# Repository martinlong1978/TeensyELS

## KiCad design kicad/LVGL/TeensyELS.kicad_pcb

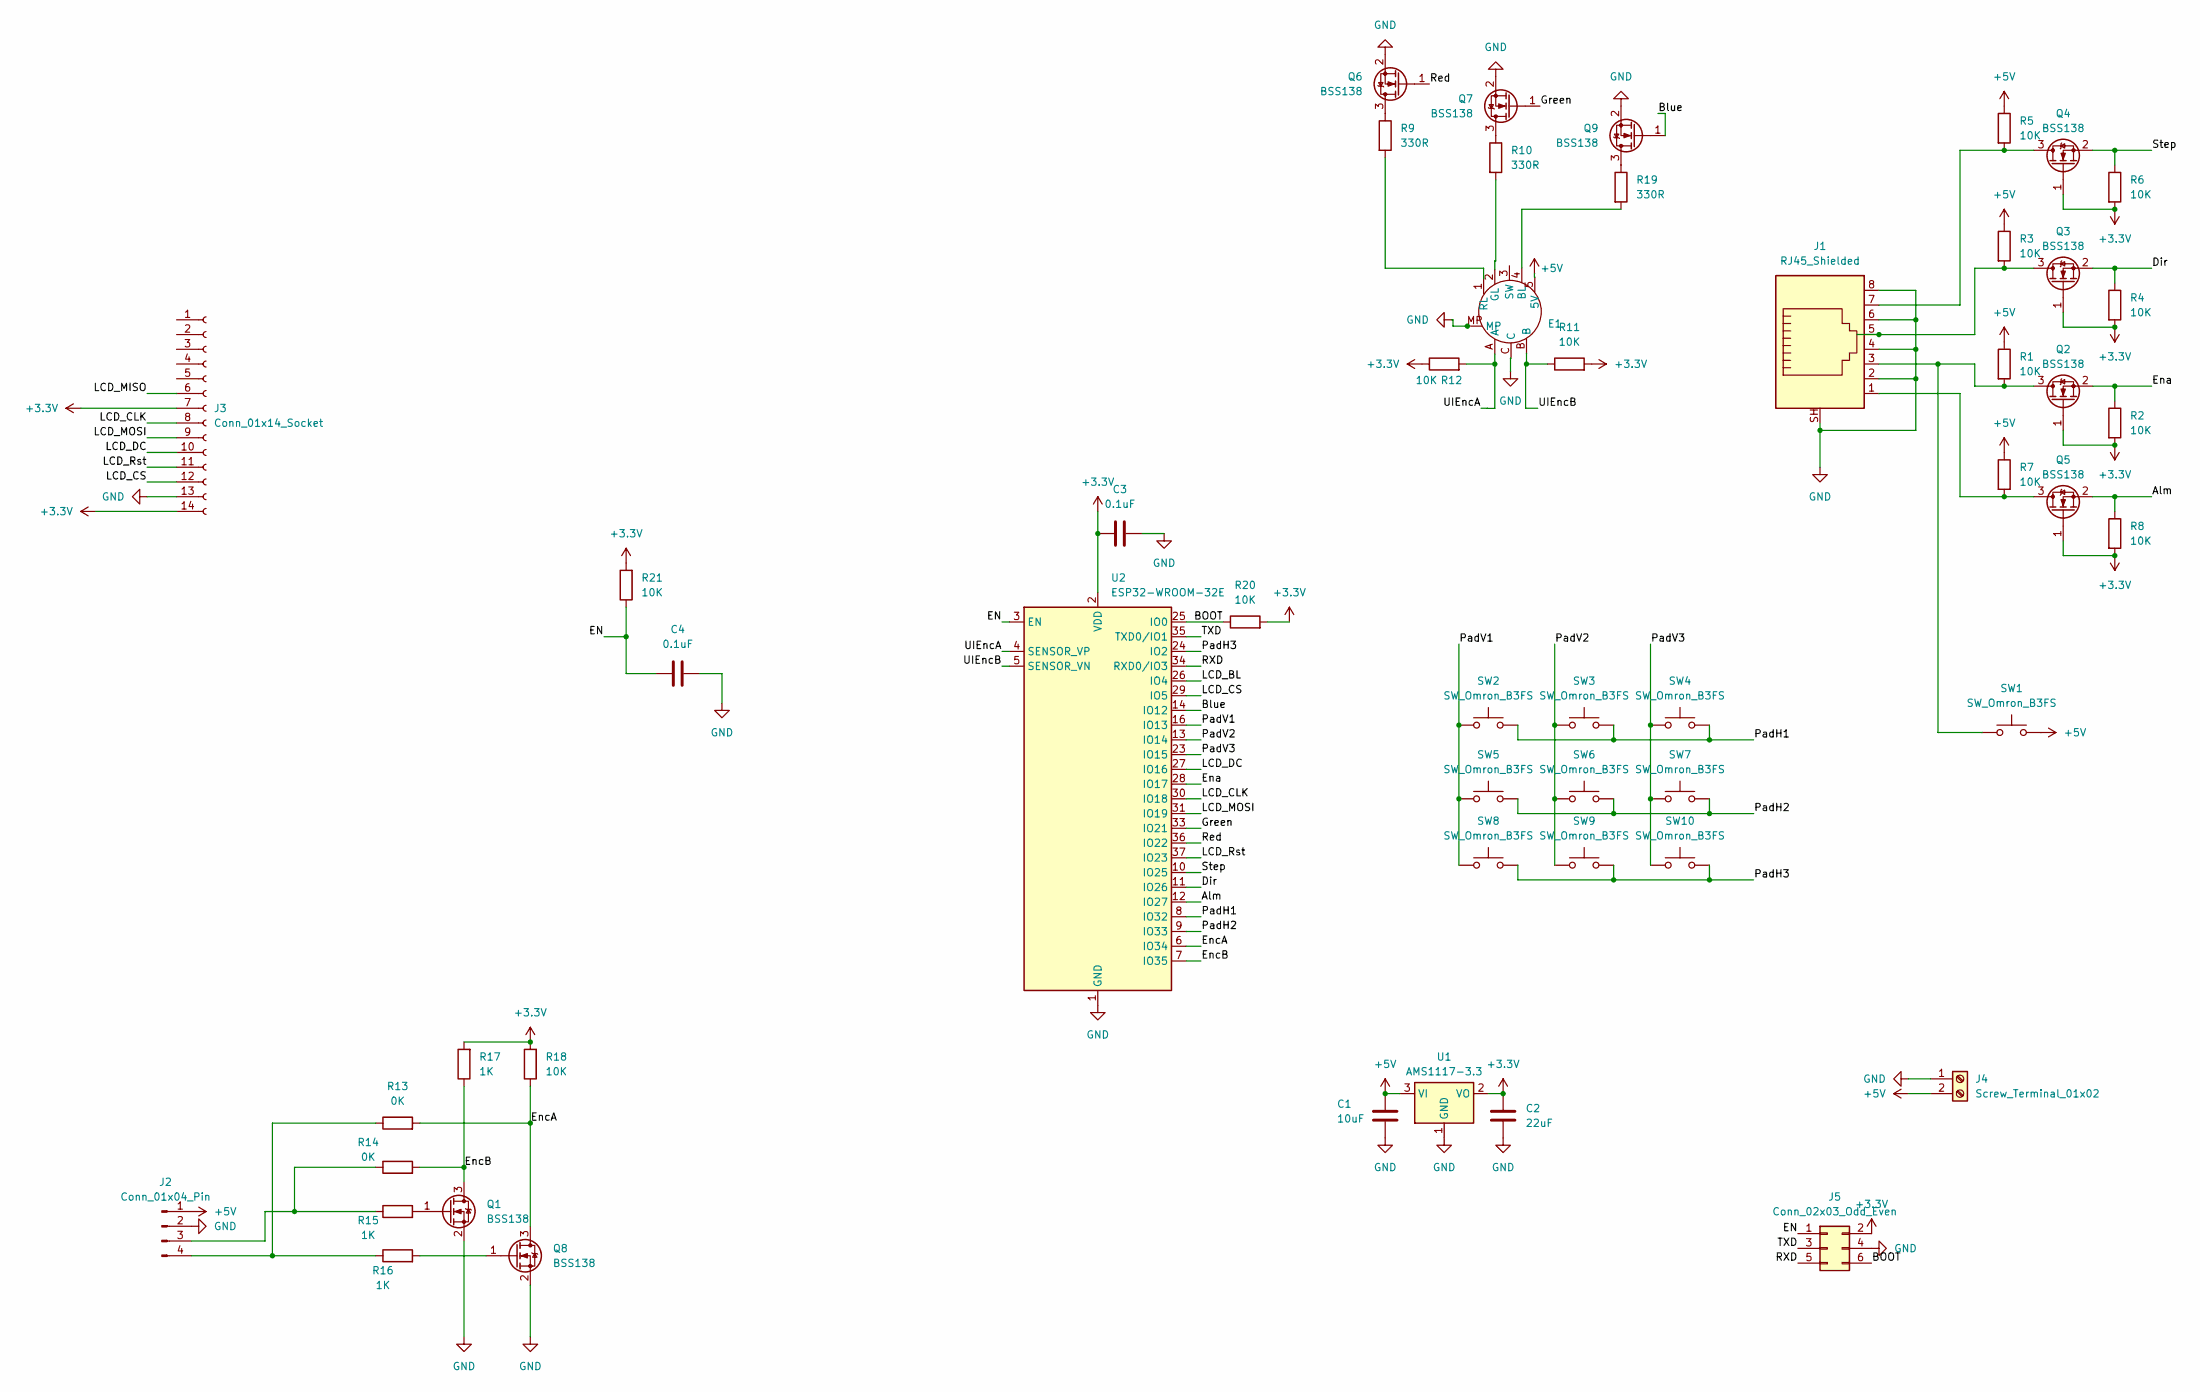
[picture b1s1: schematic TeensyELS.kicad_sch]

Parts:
C1: 10uF; C_0805_2012Metric
C2: 22uF; C_0805_2012Metric
C3, C4: 0.1uF; C_0805_2012Metric
E1: Sparkfun
J1: RJ45_Shielded; RJ45_RCH_RC01937
J2: Conn_01x04_Pin; JST_XH_B4B-XH-A_1x04_P2.50mm_Vertical
J3: Conn_01x14_Socket; PinHeader_1x14_P2.54mm_Vertical
J4: Screw_Terminal_01x02; TerminalBlock_CUI_TB007-508-02_1x02_P5.08mm_Horizontal
J5: Conn_02x03_Odd_Even; PinHeader_2x03_P1.27mm_Vertical_SMD
Q1, Q2, Q3, Q4, Q5, Q6, Q7, Q8, Q9: BSS138; SOT-23
R1, R2, R3, R4, R5, R6, R7, R8, R11, R12, R18, R20, R21: 10K; R_0805_2012Metric
R9, R10, R19: 330R; R_0805_2012Metric
R13, R14: 0K; R_0805_2012Metric
R15, R16, R17: 1K; R_0805_2012Metric
SW1, SW2, SW3, SW4, SW5, SW6, SW7, SW8, SW9, SW10: SW_Omron_B3FS; SW_TH_Tactile_Omron_B3F-10xx
U1: AMS1117-3.3; SOT-223-3_TabPin2
U2: ESP32-WROOM-32E; ESP32-WROOM-32D

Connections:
+3.3V: C2.2, C3.1, J3.7, J3.14, J5.2, Q2.1 (G), Q3.1 (G), Q4.1 (G), Q5.1 (G), R2.2, R4.2, R6.2, R8.2, R11.2, R12.1, R17.2, R18.2, R20.2, R21.2, U1.2 (VO), U2.2 (VDD)
+5V: C1.2, E1.5 (5V), J2.1, J4.2, R1.1, R3.1, R5.1, R7.1, SW1.2, U1.3 (VI)
/Alm: Q5.2 (S), R8.1, U2.12 (IO27)
/BOOT: J5.6, R20.1, U2.25 (IO0)
/Blue: Q9.1 (G), U2.14 (IO12)
/Dir: Q3.2 (S), R4.1, U2.11 (IO26)
/EN: C4.1, J5.1, R21.1, U2.3 (EN)
/Ena: Q2.2 (S), R2.1, U2.28 (IO17)
/EncA: Q8.3 (D), R13.2, R18.1, U2.6 (IO34)
/EncB: Q1.3 (D), R14.2, R17.1, U2.7 (IO35)
/Green: Q7.1 (G), U2.33 (IO21)
/LCD_BL: U2.26 (IO4)
/LCD_CLK: J3.8, U2.30 (IO18)
/LCD_CS: J3.12, U2.29 (IO5)
/LCD_DC: J3.10, U2.27 (IO16)
/LCD_MISO: J3.6
/LCD_MOSI: J3.9, U2.31 (IO19)
/LCD_Rst: J3.11, U2.37 (IO23)
/PadH1: SW2.2, SW3.2, SW4.2, U2.8 (IO32)
/PadH2: SW5.2, SW6.2, SW7.2, U2.9 (IO33)
/PadH3: SW8.2, SW9.2, SW10.2, U2.24 (IO2)
/PadV1: SW2.1, SW5.1, SW8.1, U2.16 (IO13)
/PadV2: SW3.1, SW6.1, SW9.1, U2.13 (IO14)
/PadV3: SW4.1, SW7.1, SW10.1, U2.23 (IO15)
/RXD: J5.5, U2.34 (RXD0/IO3)
/Red: Q6.1 (G), U2.36 (IO22)
/Step: Q4.2 (S), R6.1, U2.10 (IO25)
/TXD: J5.3, U2.35 (TXD0/IO1)
/UIEncA: E1.A, R12.2, U2.4 (SENSOR_VP)
/UIEncB: E1.B, R11.1, U2.5 (SENSOR_VN)
GND: C1.1, C2.1, C3.2, C4.2, E1.C, E1.MP, J1.2, J1.4, J1.6, J1.8, J1.SH, J2.2, J3.13, J4.1, J5.4, Q1.2 (S), Q6.2 (S), Q7.2 (S), Q8.2 (S), Q9.2 (S), U1.1 (GND), U2.1 (GND), U2.15 (GND), U2.38 (GND), U2.39 (GND)
unnamed: E1.4 (BL), R19.2
unnamed: E1.2 (GL), R10.2
unnamed: E1.1 (RL), R9.2
unnamed: J2.3, R14.1, R15.1
unnamed: J2.4, R13.1, R16.1
unnamed: Q1.1 (G), R15.2
unnamed: J1.3, Q2.3 (D), R1.2, SW1.1
unnamed: J1.5, Q3.3 (D), R3.2
unnamed: J1.7, Q4.3 (D), R5.2
unnamed: J1.1, Q5.3 (D), R7.2
unnamed: Q6.3 (D), R9.1
unnamed: Q7.3 (D), R10.1
unnamed: Q8.1 (G), R16.2
unnamed: Q9.3 (D), R19.1

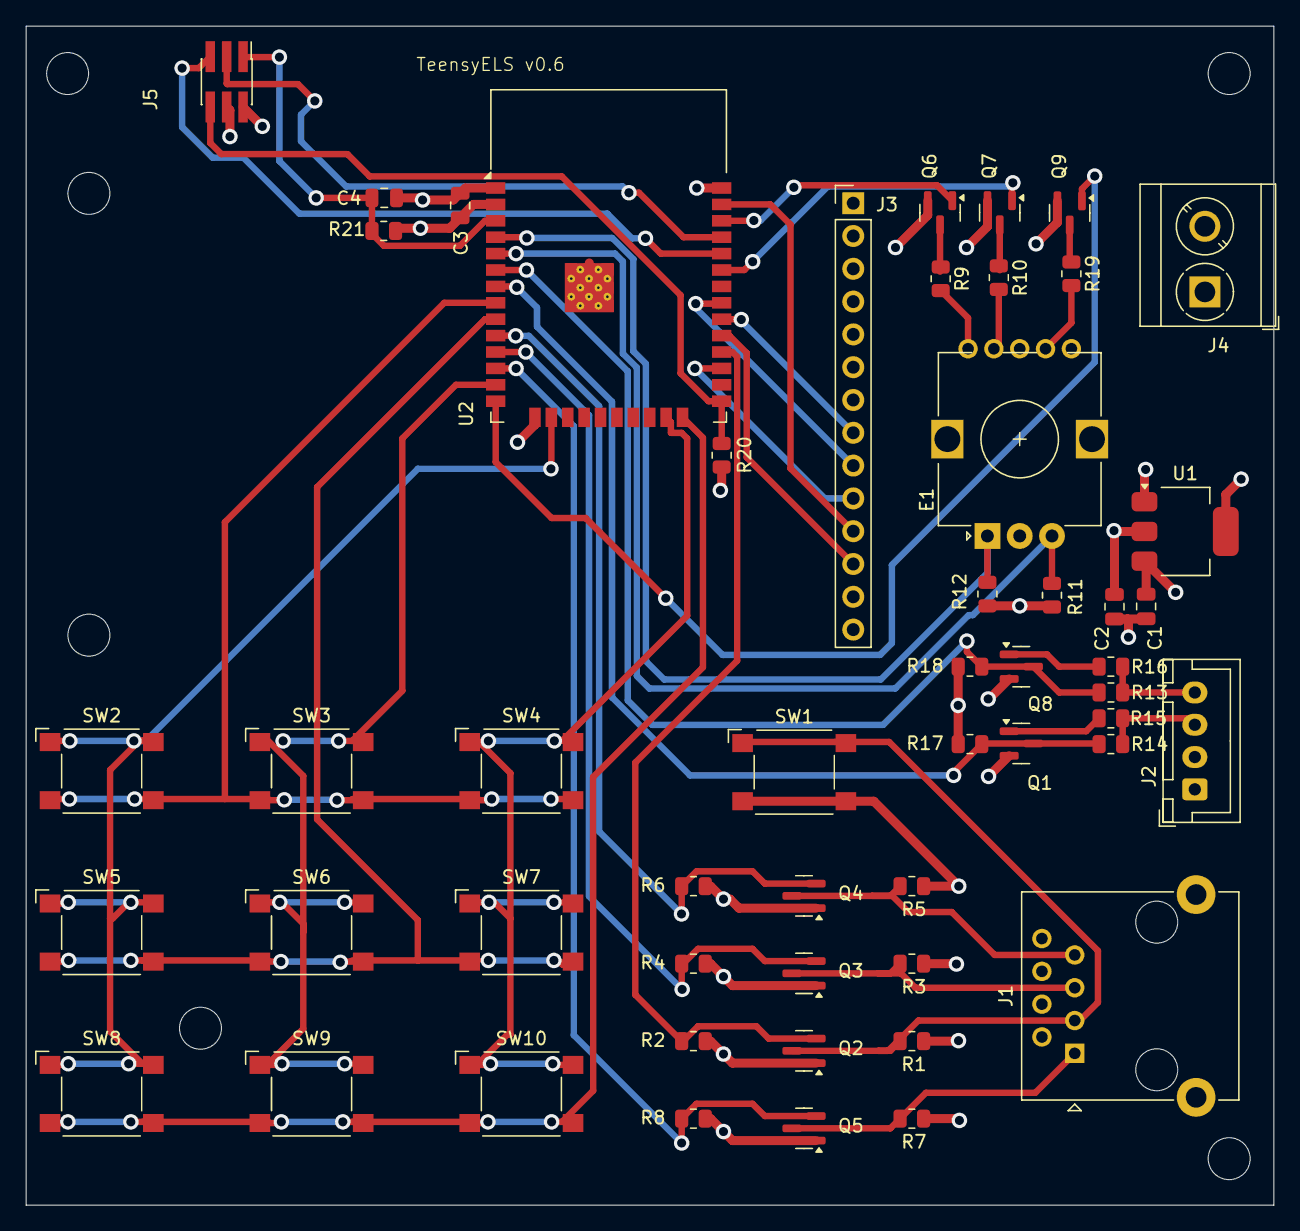
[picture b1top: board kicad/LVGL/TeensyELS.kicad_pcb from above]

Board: 4 copper layers, 96.6 x 91.3 mm, 52 parts (0 on the bottom side), 43 nets.

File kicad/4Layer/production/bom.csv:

Designator,Footprint,Quantity,Value,LCSC Part #
"_4, _3, _2, ",,4,,
E1,Sparkfun,1,~,
J1,RJ45_RCH_RC01937,1,RJ45_Shielded,
J2,JST_XH_B4B-XH-A_1x04_P2.50mm_Vertical,1,Conn_01x04_Pin,
J3,PinHeader_1x04_P2.54mm_Vertical,1,Conn_01x04_Pin,
J4,TerminalBlock_CUI_TB007-508-02_1x02_P5.08mm_Horizontal,1,Screw_Terminal_01x02,
MCU1,TTGO-T-Display,1,TTGO-T-Display,
"Q1, Q2, Q3, Q4, Q5, Q6, Q7, Q8",SOT-23,8,BSS138,
"R1, R11, R12, R18, R2, R3, R4, R5, R6, R7, R8",0805,11,10K,
"R10, R9",0805,2,330R,
"R13, R14",0805,2,0K,
"R15, R16, R17",0805,3,1K,
"SW1, SW10, SW2, SW3, SW4, SW5, SW6, SW7, SW8, SW9",SW_TH_Tactile_Omron_B3F-10xx,10,SW_Omron_B3FS,
U1,Teensy41,1,Teensy4.1,

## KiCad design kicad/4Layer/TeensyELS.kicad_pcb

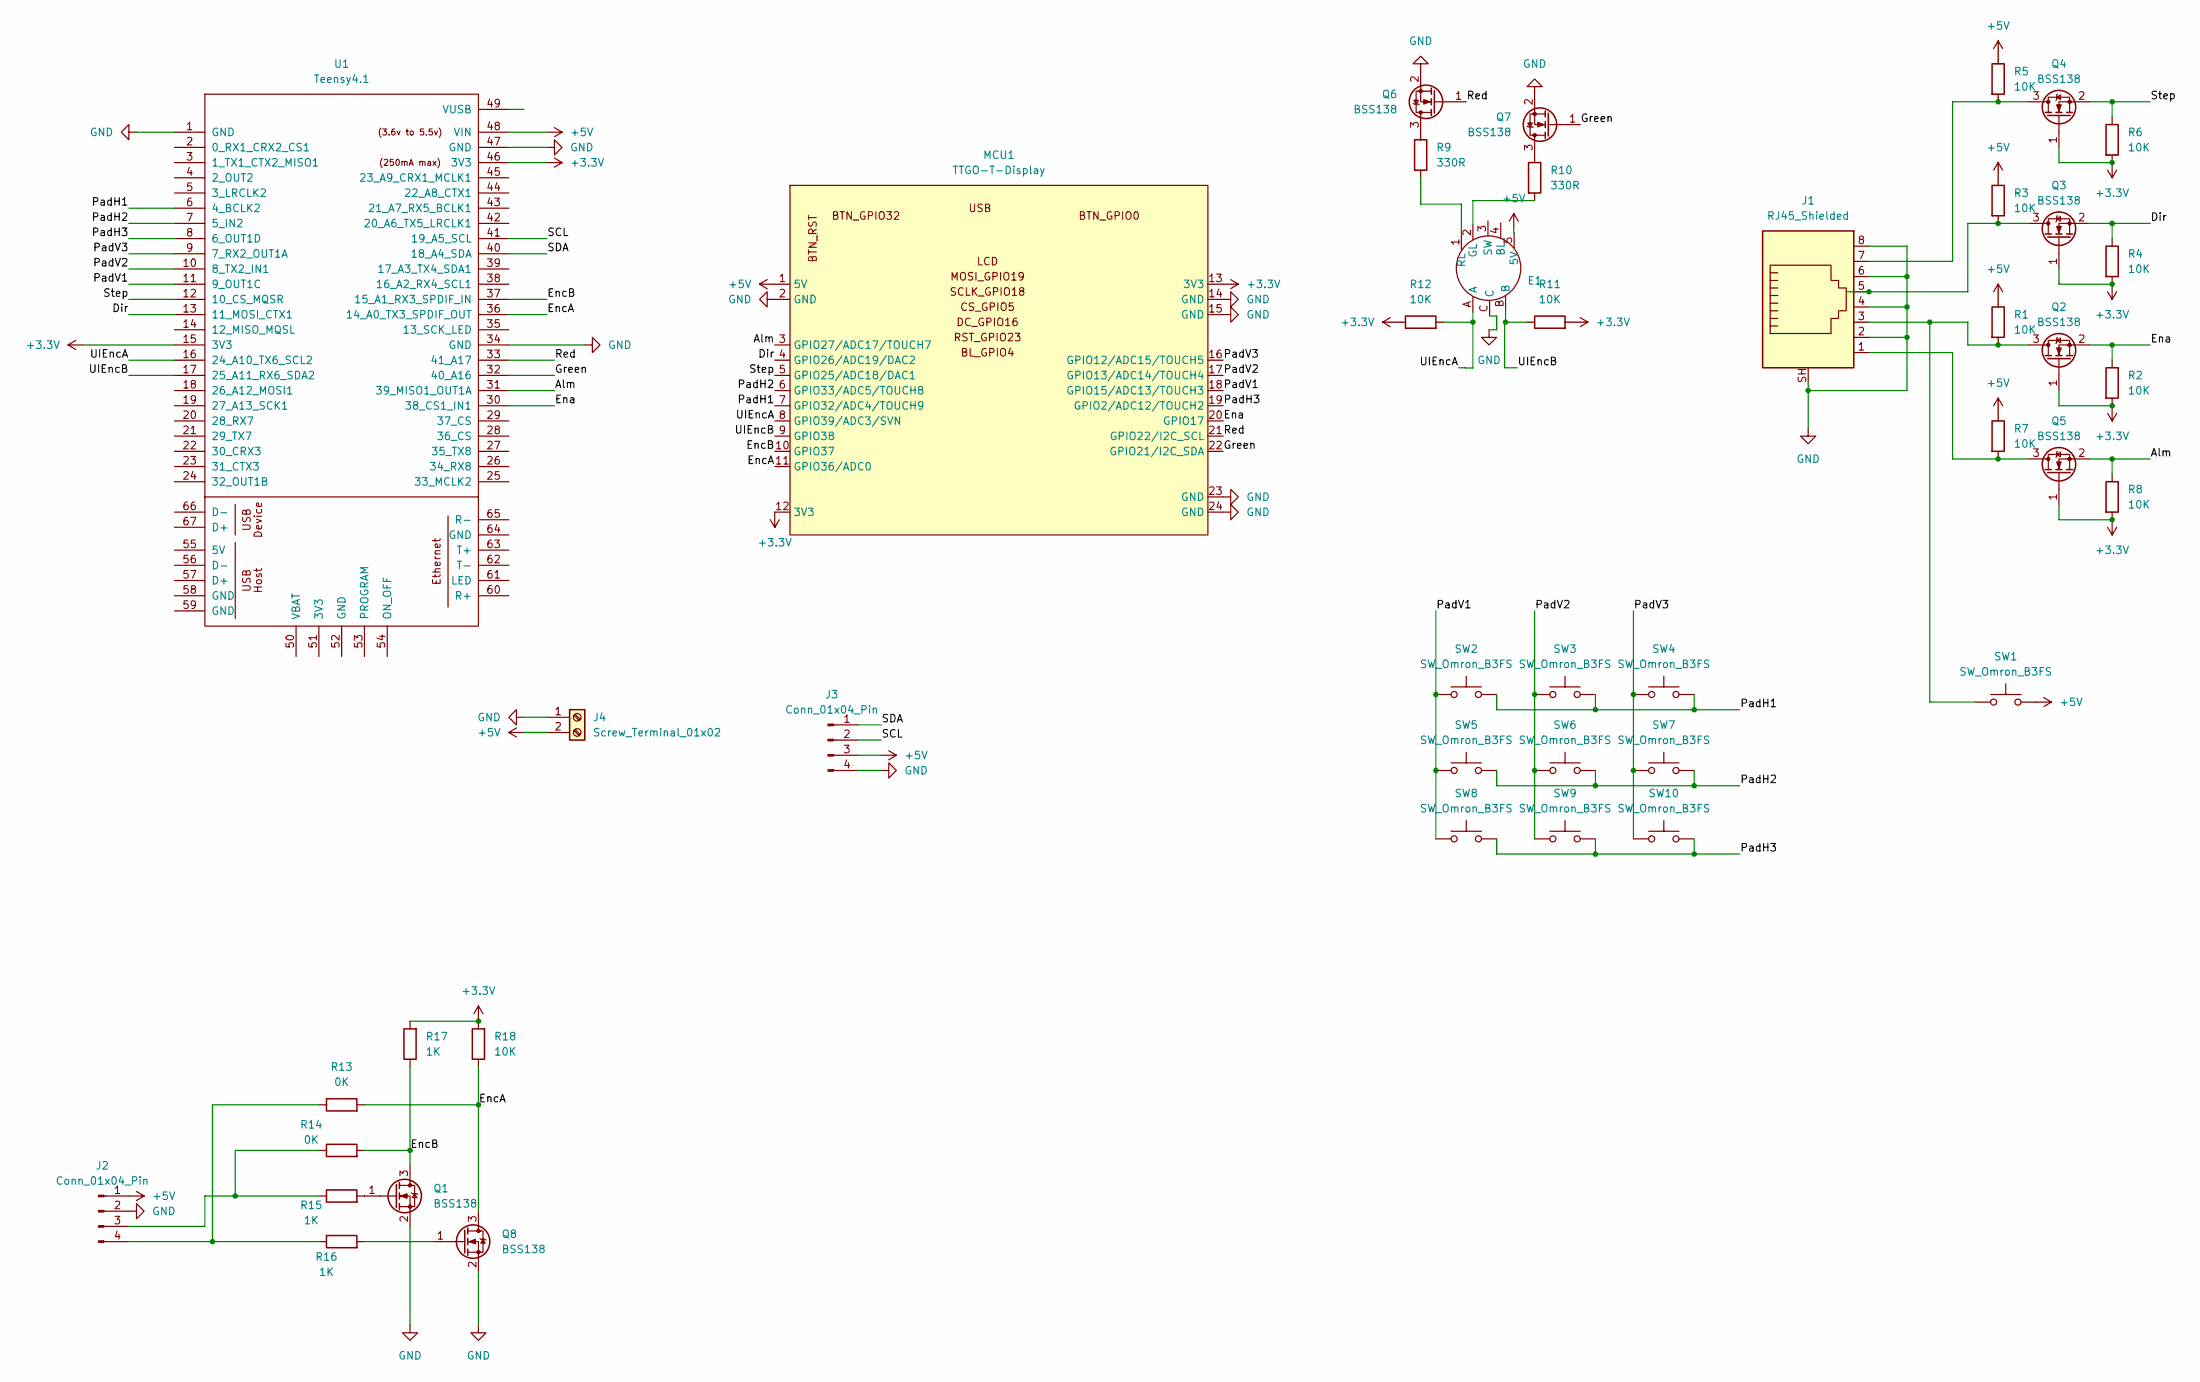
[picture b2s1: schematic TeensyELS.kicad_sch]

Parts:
E1: Sparkfun
J1: RJ45_Shielded; RJ45_RCH_RC01937
J2: Conn_01x04_Pin; JST_XH_B4B-XH-A_1x04_P2.50mm_Vertical
J3: Conn_01x04_Pin; PinHeader_1x04_P2.54mm_Vertical
J4: Screw_Terminal_01x02; TerminalBlock_CUI_TB007-508-02_1x02_P5.08mm_Horizontal
MCU1: TTGO-T-Display
Q1, Q2, Q3, Q4, Q5, Q6, Q7, Q8: BSS138; SOT-23
R1, R2, R3, R4, R5, R6, R7, R8, R11, R12, R18: 10K; R_0805_2012Metric
R9, R10: 330R; R_0805_2012Metric
R13, R14: 0K; R_0805_2012Metric
R15, R16, R17: 1K; R_0805_2012Metric
SW1, SW2, SW3, SW4, SW5, SW6, SW7, SW8, SW9, SW10: SW_Omron_B3FS; SW_TH_Tactile_Omron_B3F-10xx
U1: Teensy4.1; Teensy41

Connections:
+3.3V: MCU1.12 (3V3), MCU1.13 (3V3), Q2.1 (G), Q3.1 (G), Q4.1 (G), Q5.1 (G), R2.2, R4.2, R6.2, R8.2, R11.2, R12.1, R17.2, R18.2, U1.15 (3V3), U1.46 (3V3)
+5V: E1.5 (5V), J2.1, J3.3, J4.2, MCU1.1 (5V), R1.1, R3.1, R5.1, R7.1, SW1.2, U1.48 (VIN)
/Alm: MCU1.3 (GPIO27/ADC17/TOUCH7), Q5.2 (S), R8.1, U1.31 (39_MISO1_OUT1A)
/Dir: MCU1.4 (GPIO26/ADC19/DAC2), Q3.2 (S), R4.1, U1.13 (11_MOSI_CTX1)
/Ena: MCU1.20 (GPIO17), Q2.2 (S), R2.1, U1.30 (38_CS1_IN1)
/EncA: MCU1.11 (GPIO36/ADC0), Q8.3 (D), R13.2, R18.1, U1.36 (14_A0_TX3_SPDIF_OUT)
/EncB: MCU1.10 (GPIO37), Q1.3 (D), R14.2, R17.1, U1.37 (15_A1_RX3_SPDIF_IN)
/Green: MCU1.22 (GPIO21/I2C_SDA), Q7.1 (G), U1.32 (40_A16)
/PadH1: MCU1.7 (GPIO32/ADC4/TOUCH9), SW2.2, SW3.2, SW4.2, U1.6 (4_BCLK2)
/PadH2: MCU1.6 (GPIO33/ADC5/TOUCH8), SW5.2, SW6.2, SW7.2, U1.7 (5_IN2)
/PadH3: MCU1.19 (GPIO2/ADC12/TOUCH2), SW8.2, SW9.2, SW10.2, U1.8 (6_OUT1D)
/PadV1: MCU1.18 (GPIO15/ADC13/TOUCH3), SW2.1, SW5.1, SW8.1, U1.11 (9_OUT1C)
/PadV2: MCU1.17 (GPIO13/ADC14/TOUCH4), SW3.1, SW6.1, SW9.1, U1.10 (8_TX2_IN1)
/PadV3: MCU1.16 (GPIO12/ADC15/TOUCH5), SW4.1, SW7.1, SW10.1, U1.9 (7_RX2_OUT1A)
/Red: MCU1.21 (GPIO22/I2C_SCL), Q6.1 (G), U1.33 (41_A17)
/SCL: J3.2, U1.41 (19_A5_SCL)
/SDA: J3.1, U1.40 (18_A4_SDA)
/Step: MCU1.5 (GPIO25/ADC18/DAC1), Q4.2 (S), R6.1, U1.12 (10_CS_MQSR)
/UIEncA: E1.A, MCU1.8 (GPIO39/ADC3/SVN), R12.2, U1.16 (24_A10_TX6_SCL2)
/UIEncB: E1.B, MCU1.9 (GPIO38), R11.1, U1.17 (25_A11_RX6_SDA2)
GND: E1.C, J1.2, J1.4, J1.6, J1.8, J1.SH, J2.2, J3.4, J4.1, MCU1.2 (GND), MCU1.14 (GND), MCU1.15 (GND), MCU1.23 (GND), MCU1.24 (GND), Q1.2 (S), Q6.2 (S), Q7.2 (S), Q8.2 (S), U1.1 (GND), U1.34 (GND), U1.47 (GND)
unnamed: E1.2 (GL), R10.2
unnamed: E1.1 (RL), R9.2
unnamed: J2.3, R14.1, R15.1
unnamed: J2.4, R13.1, R16.1
unnamed: Q1.1 (G), R15.2
unnamed: J1.3, Q2.3 (D), R1.2, SW1.1
unnamed: J1.5, Q3.3 (D), R3.2
unnamed: J1.7, Q4.3 (D), R5.2
unnamed: J1.1, Q5.3 (D), R7.2
unnamed: Q6.3 (D), R9.1
unnamed: Q7.3 (D), R10.1
unnamed: Q8.1 (G), R16.2

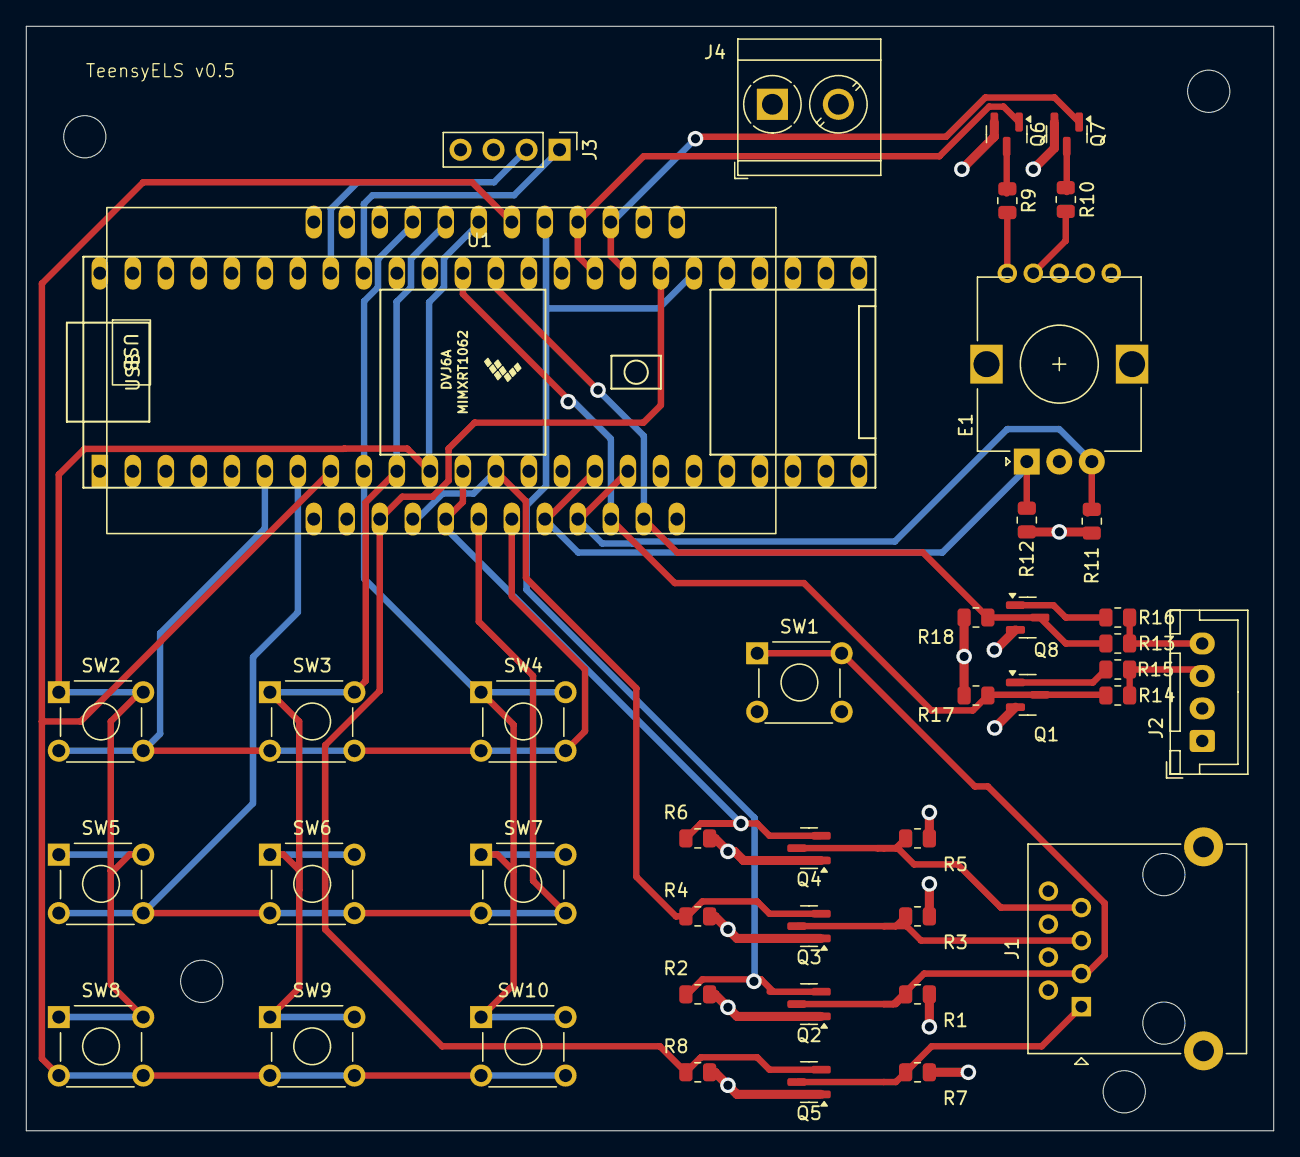
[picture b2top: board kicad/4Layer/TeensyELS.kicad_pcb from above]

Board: 4 copper layers, 96.0 x 85.0 mm, 43 parts (0 on the bottom side), 33 nets.

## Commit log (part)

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2025-01-04 WIP Esp32 support
2025-01-04 Update the encoder stuff for ESP32
2025-01-04 Made main.cpp work with both Teensy and ESP32
2025-01-05 Fixed compile
2025-01-05 Working buttons
2025-01-05 Removed blink from display. Disambiguated some constants.
2025-01-05 Added SYNC to display
2025-01-05 Fixes to Teensy build after refactor.
2025-01-05 More build fixes
2025-01-07 Tweaks to get stepper and encoder working
2025-01-09 Make the keypad more stable
2025-01-11 Adding UI Encoder
2025-01-12 Updated vs settings
2025-01-12 Decrease screen refresh to 4 fps
2025-01-12 Better FreeRTOS thread initialisation
2025-01-12 Better RPM calculation for ESP32
2025-01-12 Some display layout tweaks for TFT
2025-01-12 Teensy build fixes
2025-01-12 Fix memory shortage in display thread
2025-01-12 Fix inverted ratio calculation for leadscrew
2025-01-21 Fix steps/mm calculation to incorporate gearbox ration
2025-01-31 Added basic kicad board design
2025-01-31 Fixed missing traces
2025-01-31 Added 4 layer board
2025-01-31 Updated board version
2025-02-03 Fix incorrect pin usage
2025-02-03 Updated 2 layer designs
2025-02-03 Removed lock files
2025-02-04 Update encoder reference pos, even when keypad is locked
2025-02-17 Updated board design to fix incorrect pin usage
2025-02-17 Fixed LED function when lock button pressed.
2025-02-17 Add alternating colour for locked AND enabled state
2025-02-17 Create a stabilised tick for the display function.
2025-02-21 Use RMT for efficient pulsing
2025-02-22 Use optimised GPOI writes for ESP32
2025-02-22 Inver screen and buttons
2025-02-22 Add self-update over wifi
2025-02-22 Ignore secrets file to prevent accidental commit
2025-02-23 Added sample secrets.h file
2025-02-24 Improved debugging and OTA updating
2025-02-25 Jog icon
2025-03-09 Add JOG_LEFT and JOG_RIGHT motion states
2025-03-09 Rearrange target pitch formula
2025-03-09 Don't stop with 1 rev of endstop. STop at the endstop
2025-03-09 Fix JOG related compile errors
2025-03-09 Disable at end stop for ENABLED mm too
2025-03-09 Revert "Don't stop with 1 rev of endstop. STop at the endstop"
    This reverts commit 3a24a99c1fcc9cacbcf515619ef7a2f2ed0bffd7.
2025-03-09 Clarify comment
2025-03-09 Fix compilation for both platforms
2025-03-09 Get unit tests building
2025-03-09 Setup for debugging locally
2025-03-09 Improved test parameters
2025-03-30 Stable and working on Martin's lathe
2025-03-30 Cleanuo
2025-03-30 Ratio fix
2025-03-30 Ignore csv files
2025-04-04 Fully syncing now on ESP32
2025-04-04 Removed a bunch of debug stuff
2025-04-04 Removed elapsedmillis and use exclusively calls to micros()
2025-04-04 Split display implementations into separate files
2025-04-04 Separate out ESP/Teensy leadscrew io implementations
2025-04-04 Removed debug prints, and fixed compile for teensy.
2025-04-12 Add serial debug
2025-04-12 Rearrange sync position calc
2025-04-12 Added documentation
2025-04-12 Trying some presync stuff
2025-04-27 Remove unnecessary scaling code
2025-05-05 Fixed wifi updates
2025-05-05 Add display reset capability
2025-05-05 Standardise defines
2025-05-05 Removed button reference comments
2025-05-05 Don't tie display to board config
2025-05-05 Added units
2025-05-05 Put all UI encoder logic behind #ifdef
2025-05-05 Moved implementations to globalstate.cpp
2025-05-05 Removed ununsed define
2025-05-05 Re-unify spindle.h
2025-05-05 Renamed commsmanager
2025-05-05 Added secrets-sample.h to .gitignore
2025-05-12 WIP Optimising jog mode
2025-05-12 Stop fetching the globalstate singleton every time
2025-05-12 Fixed initialisation order
2025-05-12 Increase thread memory
2025-05-13 Init interrupts on correct core
2025-05-14 Don't set sync for jog functions
2025-05-14 Don't set sync for jog mode
2025-05-15 Refactor
2025-05-15 Re-fix jog
2025-05-16 Working optimised sync start
2025-06-05 Sync start optimisation
2025-10-30 Added test spindle
    Fix member names
    Parameterise spindle test speed
    Display signed RPM
2025-10-30 Working leadscrew optisation
2025-10-30 Decellerate on disable
2025-10-30 Fix judder on decelleration
2025-11-02 Updated config etc
2025-11-02 WIP interactive jogging
2025-11-02 Working interactive jog.
2025-11-02 Add decelleration mode for smooth stops after jogging
2025-11-02 Improved button handling stability
2025-11-02 Bring the display config into the project
2025-11-02 Updated display for jogging
2025-11-03 Jog mode, including speed selection
2025-11-04 Basic LVGL support
2025-11-04 Working bitmap
2025-11-06 Implemented all main UI changes
2025-11-06 Added symbol for jog mode
2025-11-08 LVGLCircuitBoard
2025-11-09 Updated fab files
2025-11-09 Removed non-tracking files
2025-11-10 Tidied up displays, and added partition table.
2025-11-10 Added basic AP support
2025-11-10 Saving and fetching wifi configuration data
2025-11-24 Updated kicad files
2025-11-24 Added web interface and AP mode for configuring wifi
2025-11-24 Updated pins for new board
2025-11-24 Made jog mode another motion mode
2025-11-24 Fixed encoder direction.
2026-01-20 Remove obsolete tests
2026-01-20 Move board config to separate file
2026-01-20 Remove Teensy support
2026-02-01 Made all lathe properties configurable via web.
2026-02-01 Improved websetting experience
